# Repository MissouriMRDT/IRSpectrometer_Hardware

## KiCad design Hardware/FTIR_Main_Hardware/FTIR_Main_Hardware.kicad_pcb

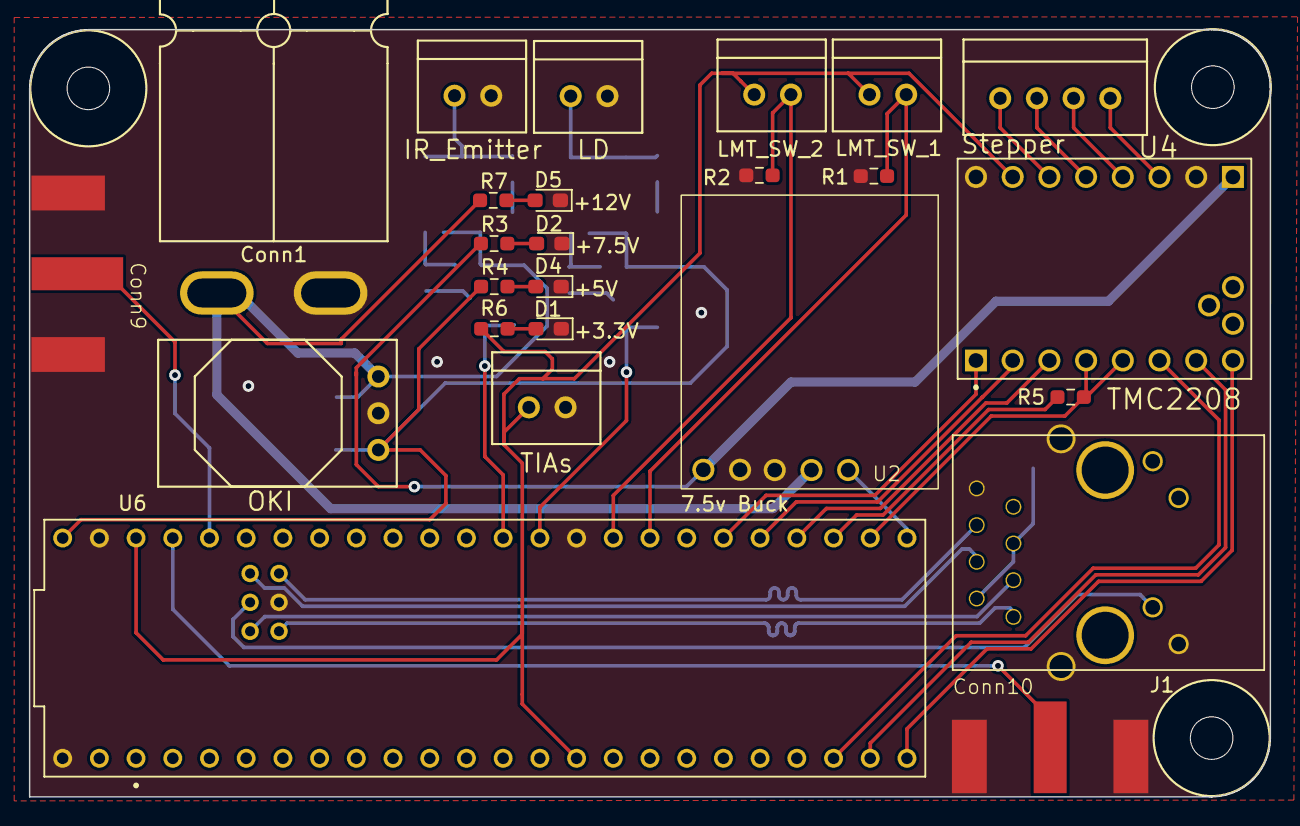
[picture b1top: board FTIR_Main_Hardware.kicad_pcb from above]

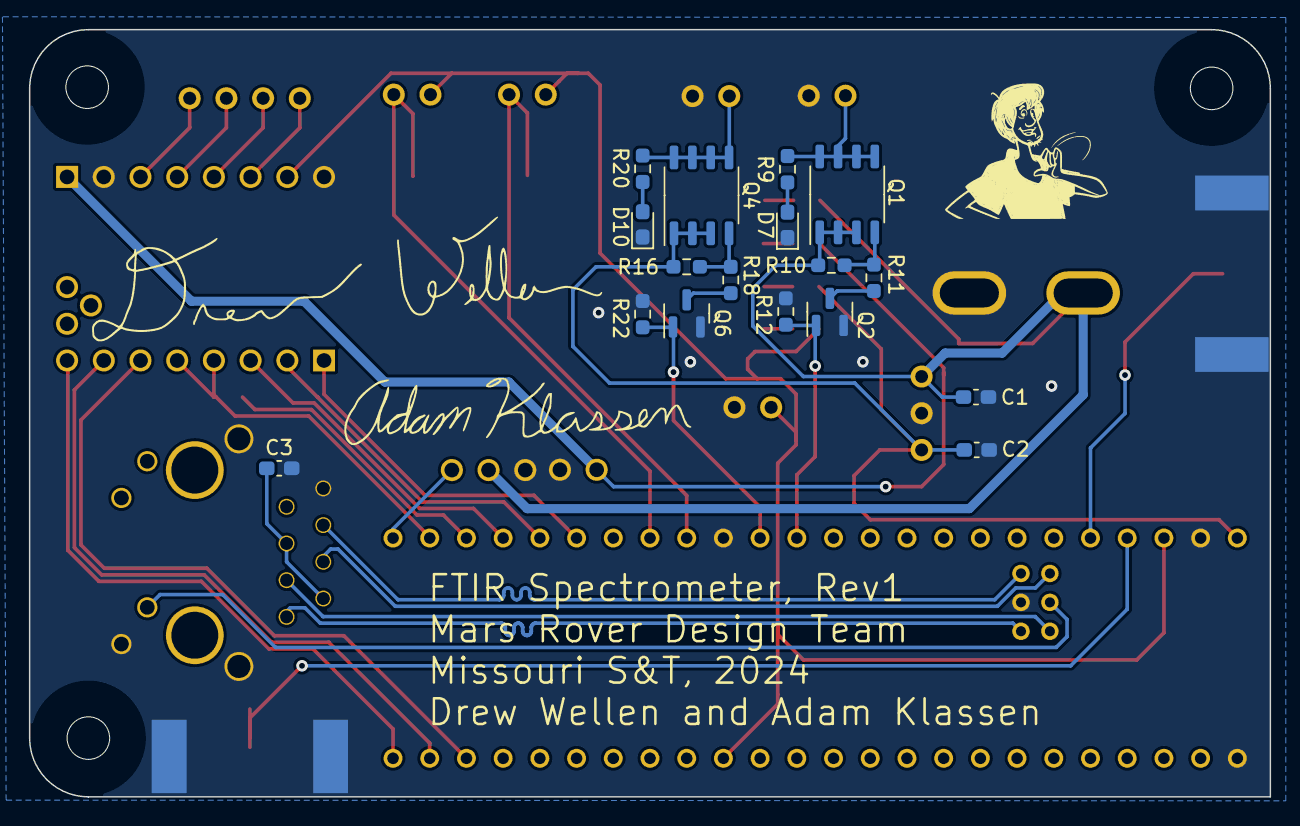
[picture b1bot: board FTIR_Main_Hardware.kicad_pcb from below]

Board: 2 copper layers, 85.9 x 53.1 mm, 45 parts (17 on the bottom side), 42 nets.

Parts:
C1, C2: 10uF; C_0603_1608Metric_Pad1.08x0.95mm_HandSolder
C3: 0.1uF; C_0603_1608Metric_Pad1.08x0.95mm_HandSolder
Conn1: AndersonPP; Square_Anderson_2_H_Side_By_Side
Conn2: LMT_SW_2; MOLEX_SL_02_Vertical
Conn3: TIAs; MOLEX_SL_02_Vertical
Conn4: MTR_Conn; MOLEX_SL_04_Vertical
Conn6: IR_Emitter; MOLEX_SL_02_Vertical
Conn8: LMT_SW_1; MOLEX_SL_02_Vertical
Conn9: PD_2; 142-0701-801
Conn10: PD_1; 142-0701-801
Conn12: LD; MOLEX_SL_02_Vertical
D1, D2, D4, D5, D7, D10: Green; LED_0603_1608Metric_Pad1.05x0.95mm_HandSolder
H2, H3, H4: MountingHole; 4_40_Hole_Corner
J1: RJ45_LED_Shielded; RJ45_Teensy
Q1, Q4: IRF7606PBF; SOP-8_3.9x4.9mm_P1.27mm
Q2, Q6: BSS138; SOT-23
R1, R2, R12, R22: 4.7k; R_0603_1608Metric_Pad0.98x0.95mm_HandSolder
R3: 510; R_0603_1608Metric_Pad0.98x0.95mm_HandSolder
R4, R20: 300; R_0603_1608Metric_Pad0.98x0.95mm_HandSolder
R5, R7, R9: 1k; R_0603_1608Metric_Pad0.98x0.95mm_HandSolder
R6: 100; R_0603_1608Metric_Pad0.98x0.95mm_HandSolder
R10, R11, R16, R18: 10k; R_0603_1608Metric_Pad0.98x0.95mm_HandSolder
U2: D36V28F7; D36V28F7_Buck
U3: OKI; OKI_Horizontal
U4: TMC2208; MODULE_TMC2208_SILENTSTEPSTICK
U6: Teensy4.1_DEV-16771; Teensy_4_1_Ethernet

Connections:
+3V3: Conn2.1, Conn3.1, Conn8.1, R6.1, U4.VIO, U6.3.3V_1 (3.3V), U6.3.3V_2 (3.3V)
+5V: C2.1, Q4.1 (S), Q4.2 (S), Q4.3 (S), R4.2, R16.1, U3.3 (Vo), U6.VIN
+7.5V: R3.1, U2.VOUT, U4.VM
+12V: C1.1, Conn1.2, Q1.1 (S), Q1.2 (S), Q1.3 (S), R7.1, R10.1, U2.VIN, U3.1 (Vi)
BUCK_EN: U2.EN, U6.33 (MCLK2)
CLK: U4.CLK, U6.36 (CS2)
DIR: U4.DIR, U6.38 (A14)
DRIVER_EN: U4.EN, U6.32 (OUT1B)
ETH_LED: J1.10, U6.LED
GND: C1.2, C2.2, C3.2, Conn1.1 (GND), Conn3.2, Conn6.2, Conn9.2 (Sleve), Conn10.2 (Sleve), Conn12.2, D1.1 (K), D2.1 (K), D4.1 (K), D5.1 (K), D7.1 (K), D10.1 (K), J1.8, J1.9, J1.SH, Q2.2 (S), Q6.2 (S), R1.2, R2.2, R12.2, R22.2, U2.GND, U3.2 (GND), U4.GND, U6.GND1 (GND), U6.GND2 (GND), U6.GND3 (GND), U6.GND5 (GND)
LAMP_CTRL: Q2.1 (G), R12.1, U6.14 (A0)
LD_CTRL: Q6.1 (G), R22.1, U6.13 (SCK)
MS1_CTRL: U4.MS1, U6.31 (CTX3)
MS2_CTRL: U4.MS2, U6.30 (CRX3)
unnamed: C3.1, J1.2, J1.5
unnamed: Conn4.1, U4.M1B
unnamed: Conn4.2, U4.M1A
unnamed: Conn4.3, U4.M2A
unnamed: Conn4.4, U4.M2B
unnamed: Conn6.1, Q1.5 (D), Q1.6 (D), Q1.7 (D), Q1.8 (D), R9.1
unnamed: Conn9.1 (Tip), U6.22 (A8)
unnamed: Conn10.1 (Tip), U6.23 (A9)
unnamed: Conn12.1, Q4.5 (D), Q4.6 (D), Q4.7 (D), Q4.8 (D), R20.1
unnamed: D1.2 (A), R6.2
unnamed: D2.2 (A), R3.2
unnamed: D4.2 (A), R4.1
unnamed: D5.2 (A), R7.2
unnamed: D7.2 (A), R9.2
unnamed: D10.2 (A), R20.2
unnamed: Q1.4 (G), R10.2, R11.1
unnamed: Q2.3 (D), R11.2
unnamed: Q4.4 (G), R16.2, R18.1
unnamed: Q6.3 (D), R18.2
unnamed: Conn8.2, R1.1, U6.40 (A16)
unnamed: Conn2.2, R2.1, U6.41 (A17)
unnamed: R5.2, U6.35 (TX8)
R+: J1.4, U6.R+
R-: J1.6, U6.R-
STEP: U4.STEP, U6.37 (CS3)
T+: J1.1, U6.T+
T-: J1.3, U6.T-
UART: R5.1, U4.PDN_UART_1, U4.PDN_UART_2, U6.34 (RX8)

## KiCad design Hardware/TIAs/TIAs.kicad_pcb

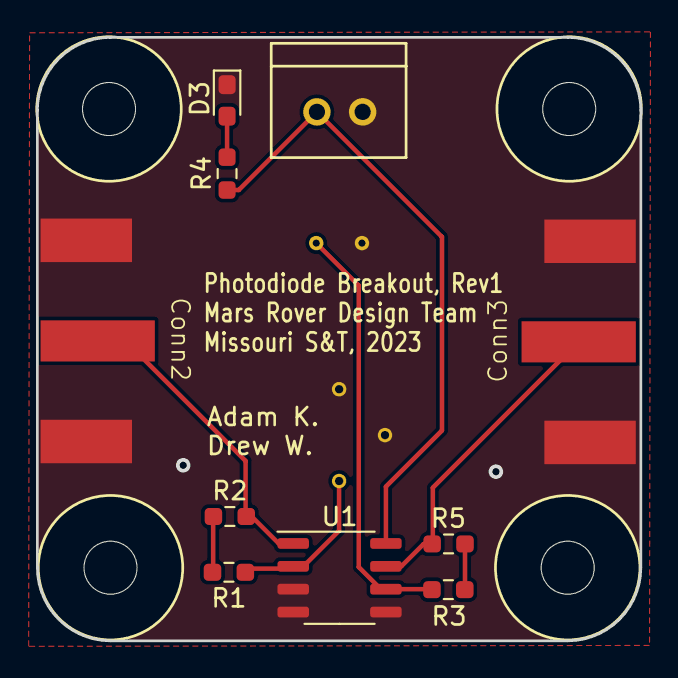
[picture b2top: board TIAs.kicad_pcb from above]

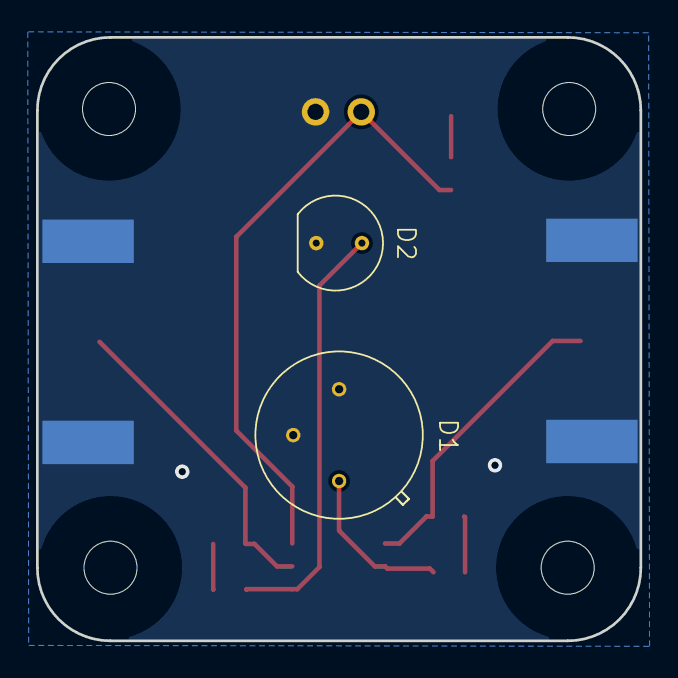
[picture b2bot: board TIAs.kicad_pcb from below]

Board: 2 copper layers, 33.5 x 33.5 mm, 16 parts (2 on the bottom side), 9 nets.

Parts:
Conn1: TIA; MOLEX_SL_02_Vertical
Conn2: PD_1; 142-0701-801
Conn3: PD_2; 142-0701-801
D1: S5971; P16113-011MN
D2: D_Photo; VTP9812FH
D3: Green; LED_0603_1608Metric_Pad1.05x0.95mm_HandSolder
H1, H2, H3, H4: MountingHole; 4_40_Hole_Corner
R1, R2, R3, R5: R_0603_1608Metric_Pad0.98x0.95mm_HandSolder
R4: 100; R_0603_1608Metric_Pad0.98x0.95mm_HandSolder
U1: Opamp_Dual; SO-8_3.9x4.9mm_P1.27mm

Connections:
+3V3: Conn1.1, R4.1, U1.8 (V+)
GND: Conn1.2, Conn2.2 (Sleve), Conn3.2 (Sleve), D1.2 (C), D1.3 (A), D2.2 (A), D3.1 (K), U1.3 (+), U1.4 (V-), U1.5 (+)
unnamed: Conn2.1 (Tip), R2.2, U1.1
unnamed: Conn3.1 (Tip), R5.2, U1.7
unnamed: D1.1 (K), R1.1, U1.2 (-)
unnamed: D2.1 (K), R3.1, U1.6 (-)
unnamed: D3.2 (A), R4.2
unnamed: R1.2, R2.1
unnamed: R3.2, R5.1

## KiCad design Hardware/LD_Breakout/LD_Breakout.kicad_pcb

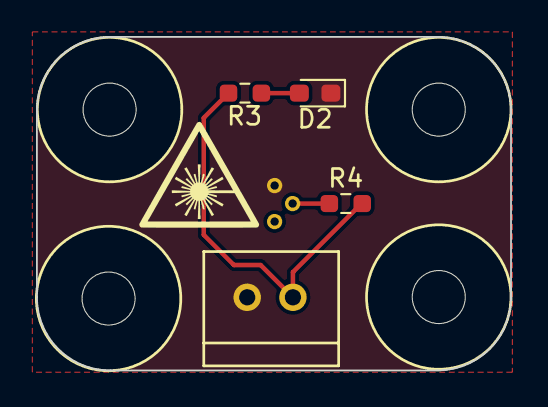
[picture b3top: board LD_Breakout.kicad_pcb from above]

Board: 2 copper layers, 26.3 x 18.5 mm, 9 parts (1 on the bottom side), 4 nets.

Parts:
Conn2: LD; MOLEX_SL_02_Vertical
D2: Green; LED_0603_1608Metric_Pad1.05x0.95mm_HandSolder
H1, H2, H3, H4: MountingHole; 4_40_Hole_Corner
LD2: D_Laser_Photo_NType; RLD63NPC5
R3: 300; R_0603_1608Metric_Pad0.98x0.95mm_HandSolder
R4: 85; R_0603_1608Metric_Pad0.98x0.95mm_HandSolder

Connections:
+5V: Conn2.1, R3.1, R4.1
GND: Conn2.2, D2.1 (K), LD2.1
unnamed: D2.2 (A), R3.2
unnamed: LD2.2, R4.2

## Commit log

2023-09-15 Made the lightbulb turn on I think
    Hey, at least it's something
2023-09-15 Amogus
    Found out it is not a good idea to put 12 volts into the teensy and that's why we need an OKI. Also 2 pin connectors are a thing.
2023-09-15 Amogus round 2
    fixed a label because Derw said it was bad
2023-09-16 Created Stepper Symbol
    TMC2208 Stepper Motor Driver and supporting circuitry.
    Drew made me delete the amogus :,(
2023-09-16 Name change
    I mistakenly named the branch after myself like we did during electrical training. The name now follows convention.
2023-09-16 File Changes
    Changed names and checked proper push
2023-09-19 Random Commit
    idk what these changes are but Drew told me to commit them
2023-09-21 File Rename
2023-09-21 Stepper Driver work and general clean-up
2023-09-21 Moved Files
2023-09-21 Added Photodetector
2023-09-22 Stepper Driver Changes
2023-09-23 Added TIA
    Transimpedence Amp for Photodetector
2023-09-23 Improved MOSFET
    Figured out how mosfet switches work
2023-09-23 Wait there were more changes
    idk what these are
2023-09-23 Stuff idk
2023-09-23 Made MOSFET work
    It was bad good thing Drew is here
2023-09-23 Added laser diode driver
2023-09-23 Page Setup
2023-09-24 New Photodetector and Laserdiode
2023-09-24 Too much
2023-09-24 Change Voltage Divider
2023-09-24 Some small changes during review
2023-09-24 Name Change
2023-09-24 File Sorting
2023-09-24 Updating from review
2023-09-25 Continuing review changes
2023-09-25 Figured out the op amps somewhat
    now uses dual op amps and the capacitance is calculated on one of them
2023-09-28 Changes to TIA
    Set reference voltage to ground and removed the voltage divider altogether
2023-09-28 Malacki changes
2023-09-29 Value changes
2023-09-29 Symbol for stepper
2023-09-29 Revert "Symbol for stepper"
    This reverts commit 3005be89c2a7f566bd27afdf3620319c1e39fccb.
2023-09-29 Added breakouts
2023-09-29 Removed more stuff
    thanks, Malacki
2023-09-29 More changes appeared
    Just to be safe.
2023-09-30 Starting BOM
2023-09-30 Separate Schematics
2023-10-01 changed resistor values
2023-10-04 Changed capacitor on OKI
    Was only rated for 10V but needed 12V. We should change the standard sheet so more people don't burn out their OKIs.
2023-10-04 Footprint assignments
2023-10-04 Minor Changes
2023-10-04 Review pt.2 changes
2023-10-14 Added Footprints
    Switched back to BMS op-amps
2023-10-14 Stepper Driver Footprint
2023-10-14 Added another footprint
2023-10-14 Laser Diode Footprint
2023-10-14 Footprints for LD and Stepper Driver fr this time
2023-10-14 Fixed footprint importing???
2023-10-14 Fixed footprints??????
2023-10-14 Checked Footprints
2023-10-15 Finished Footprints (!)
    I want to sleep :(
2023-10-15 Moved footprints to local folder
    Should work now?
2023-10-15 Began Layout
2023-10-15 updating footprint libraries
2023-10-15 Matched pin numbers between footprints and symbols
    cursed
2023-10-15 Fixed all custom footprint problems and began boards
2023-10-15 Rev1 layout ready for review
2023-10-19 Delete'd Drew's stuff
    Was bad >:(
2023-10-19 Third time's the charm
    Layout try 3
2023-10-20 Edge cuts and placing
2023-10-20 Fixed edge cut dimensions
    From center of hole mounts:
    3060 mils
    1770 mills
    From the top left to the center left:
    980 mils
2023-10-20 completed components placement
2023-10-20 Separated Layouts
2023-10-20 Moved breakout boards to separate layouts
    Edge cut no work :,(
2023-10-20 Fixed 2 wacky silly little edge cuts
    It made the board work suddenly :,)
2023-10-20 Added a few traces
    I have an 8 AM class in 5 hours :(
2023-10-20 More trace routing
2023-10-20 idk what these changes are?
    I think I edited an SMA
2023-10-21 Finished the board
    Added traces and reassigned pins
2023-10-21 Finishing touches on all boards
2023-10-21 Exported STEP files
2023-10-21 Tweaked one trace
2023-10-23 Fixed some things from the layout
    haha drew and ethan can't stop me anymore
2023-10-24 Fixed power traces
    Preventing reflections
    Stopping 12v traces from going through vias/pads
2023-10-27 Fixes to LD board
    See layout review
2023-10-27 Fixes to PD breakout
    See layout review
2023-10-27 Fixes to main board
    See layout review
2023-10-30 Added Labels
    should be ready for a board review?
2023-11-02 Fixed footprints
    Some resistors still had LED footprints which I had thought I had fixed, but failed because I did not also update the schematic.
2023-11-03 Fixed 68 errors
    It works now hopefully?
2023-11-04 Fixed silkscreen overlap
    Drew is getting errors for some reason that I don't?
2023-11-04 Wacky 12v pad?
    Idk
2023-11-04 Minor Finishing Touches
2023-11-05 Added names to mini boards
    Drew told me to
2023-11-05 Fixed UART
2023-11-05 Changed UART circuit
    Added a resistor to match this diagram:
    https://wiki.fysetc.com/TMC2208/#hardware-connection
2023-11-08 Added 3v3 indicator
    also tried to make a gerb, but I don't think it looks quite right
2023-11-08 Generated Gerbs
    Don't check anything in "Include in All Layers"
